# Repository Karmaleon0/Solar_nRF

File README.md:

A small solar-only, battery-free device that harvests energy using a single BPW34 cell, boosted and managing energy with the TI B5504.

Sending BLE advertisements every few seconds in direct sunlight - measuring the temperature using an exteral I2C digital chip connected to a Raytac nRF module.

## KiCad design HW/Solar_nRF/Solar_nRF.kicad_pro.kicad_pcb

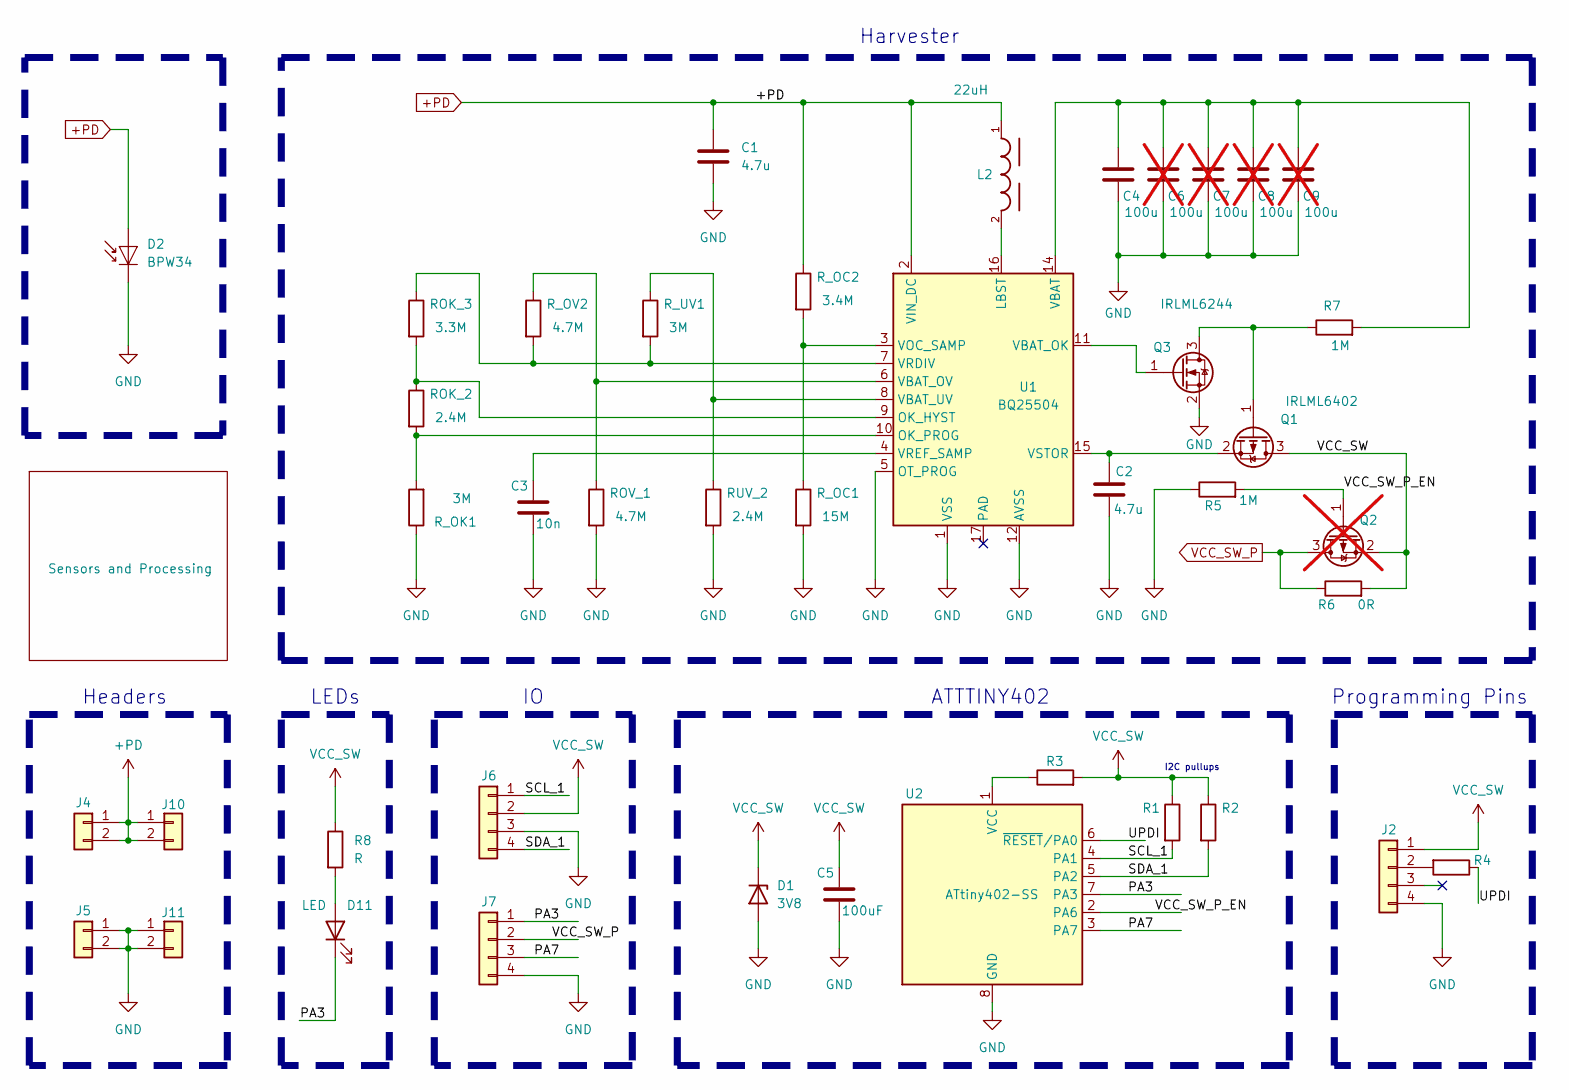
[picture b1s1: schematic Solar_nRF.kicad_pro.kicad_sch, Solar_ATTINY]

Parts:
C1, C2: 4.7u; C_0805_2012Metric_Pad1.18x1.45mm_HandSolder
C3: 10n; C_0603_1608Metric_Pad1.08x0.95mm_HandSolder
C4: 100u; C_1206_3216Metric_Pad1.33x1.80mm_HandSolder
C5: 100uF; C_1206_3216Metric_Pad1.33x1.80mm_HandSolder
C6, C7, C8, C9: 100u; C_1206_3216Metric_Pad1.33x1.80mm_HandSolder; not fitted
D1: 3V8; D_SOD-123F
D2: BPW34; Osram_DIL2_4.3x4.65mm_P5.08mm
D11: LED; LED_0805_2012Metric_Pad1.15x1.40mm_HandSolder
J2, J6, J7: Conn_01x04; PinHeader_1x04_P2.54mm_Vertical
J4, J5, J10, J11: Conn_01x02; PinSocket_1x02_P2.54mm_Vertical
L2: 22uH; WE-TPC_2828
Q1: IRLML6402; SOT-23
Q2: IRLML6402; SOT-23; not fitted
Q3: IRLML6244; SOT-23
R1, R2, R4: R; R_0603_1608Metric_Pad0.98x0.95mm_HandSolder
R3, R6: 0R; R_0603_1608Metric_Pad0.98x0.95mm_HandSolder
R5, R7: 1M; R_0603_1608Metric_Pad0.98x0.95mm_HandSolder
R8: R; R_0805_2012Metric_Pad1.20x1.40mm_HandSolder
ROK_2: 2.4M; R_0603_1608Metric_Pad0.98x0.95mm_HandSolder
ROK_3: 3.3M; R_0603_1608Metric_Pad0.98x0.95mm_HandSolder
ROV_1: 4.7M; R_0603_1608Metric_Pad0.98x0.95mm_HandSolder
RUV_2: 2.4M; R_0603_1608Metric_Pad0.98x0.95mm_HandSolder
R_OC1: 15M; R_0603_1608Metric_Pad0.98x0.95mm_HandSolder
R_OC2: 3.4M; R_0603_1608Metric_Pad0.98x0.95mm_HandSolder
R_OK1: 3M; R_0603_1608Metric_Pad0.98x0.95mm_HandSolder
R_OV2: 4.7M; R_0603_1608Metric_Pad0.98x0.95mm_HandSolder
R_UV1: 3M; R_0603_1608Metric_Pad0.98x0.95mm_HandSolder
U1: BQ25504; VQFN-16-1EP_3x3mm_P0.5mm_EP1.68x1.68mm
U2: ATtiny402-SS; SOIC-8_3.9x4.9mm_P1.27mm

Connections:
+PD: C1.1, D2.2 (A), J4.1, J4.2, J10.1, J10.2, L2.1, R_OC2.1, U1.2 (VIN_DC); also elsewhere on the board
/PA3: D11.1 (K), J7.1, U2.7 (PA3)
/PA7: J7.3, U2.3 (PA7)
/SCL_1: J6.1, R1.2, U2.4 (PA1)
/SDA_1: J6.4, R2.2, U2.5 (PA2)
/UPDI: R4.1, U2.6 (~RESET/PA0)
/VCC_SW_P_EN: Q2.1 (G), R5.2, U2.2 (PA6)
GND: C1.2, C2.2, C3.1, C4.2, C5.1, C6.2, C7.2, C8.2, C9.2, D1.2 (A), D2.1 (K), J2.4, J5.1, J5.2, J6.3, J7.4, J11.1, J11.2, Q3.2 (S), R5.1, ROV_1.2, RUV_2.2, R_OC1.2, R_OK1.1, U1.1 (VSS), U1.5 (OT_PROG), U1.12 (AVSS), U1.13 (VSS), U2.8 (GND); also elsewhere on the board
unnamed: D11.2 (A), R8.2
unnamed: J2.2, R4.2
unnamed: Q1.1 (G), Q3.3 (D), R7.1
unnamed: C2.1, Q1.2 (S), U1.15 (VSTOR)
unnamed: Q3.1 (G), U1.11 (VBAT_OK)
unnamed: L2.2, U1.16 (LBST)
unnamed: ROK_2.1, ROK_3.2, U1.9 (OK_HYST)
unnamed: ROK_2.2, R_OK1.2, U1.10 (OK_PROG)
unnamed: C4.1, C6.1, C7.1, C8.1, C9.1, R7.2, U1.14 (VBAT)
unnamed: ROV_1.1, R_OV2.1, U1.6 (VBAT_OV)
unnamed: RUV_2.1, R_UV1.1, U1.8 (VBAT_UV)
unnamed: R_OC1.1, R_OC2.2, U1.3 (VOC_SAMP)
unnamed: ROK_3.1, R_OV2.2, R_UV1.2, U1.7 (VRDIV)
unnamed: C3.2, U1.4 (VREF_SAMP)
unnamed: R3.1, U2.1 (VCC)
VCC_SW: C5.2, D1.1 (K), J2.1, J6.2, Q1.3 (D), Q2.2 (S), R1.1, R2.1, R3.2, R6.2, R8.1
VCC_SW_P: J7.2, Q2.3 (D), R6.1; also elsewhere on the board

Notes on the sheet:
Programming Pins
I2C pullups
ATTTINY402
Harvester
Headers
LEDs

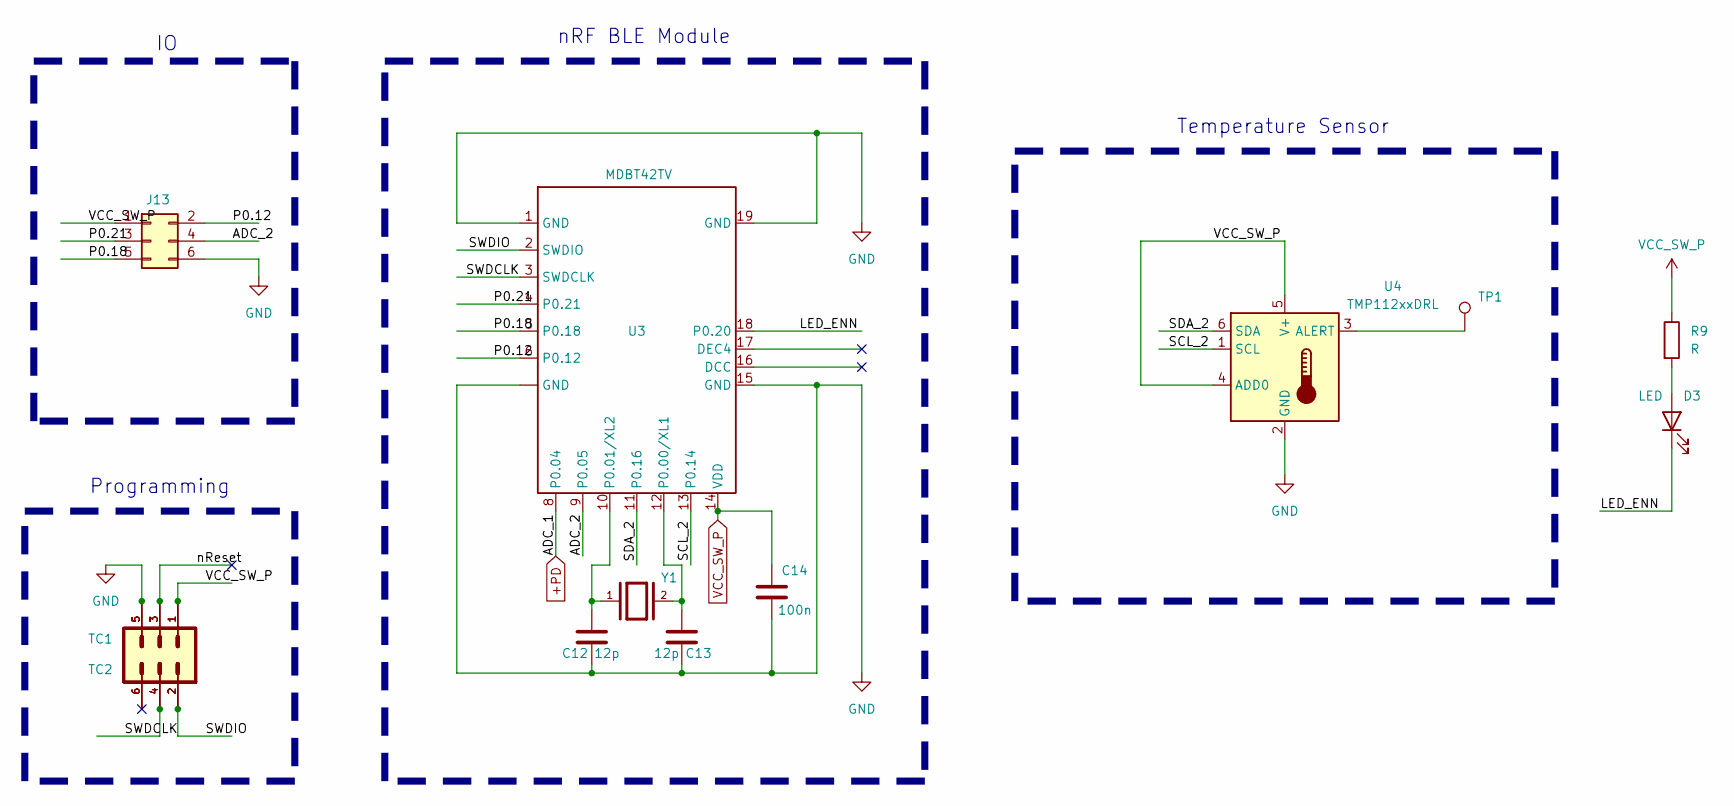
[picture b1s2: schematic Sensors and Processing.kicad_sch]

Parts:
C12, C13: 12p; C_0603_1608Metric_Pad1.08x0.95mm_HandSolder
C14: 100n; C_0805_2012Metric_Pad1.18x1.45mm_HandSolder
D3: LED; LED_0805_2012Metric_Pad1.15x1.40mm_HandSolder
J13: Conn_02x03_Odd_Even; PinHeader_2x03_P2.54mm_Vertical
R9: R; R_0805_2012Metric_Pad1.20x1.40mm_HandSolder
TC1, TC2: TC2030-IDC
TP1: TestPoint; TestPoint_Pad_D1.0mm
U3: MDBT42TV; MDBT42TV-P
U4: TMP112xxDRL; SOT-563
Y1: ABS07-32.768KHZ-T; XTAL_ABS07-32.768KHZ-T; PARTREV 08.19.15

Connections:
+PD: U3.8 (P0.04); also elsewhere on the board
/Sensors and Processing/ADC_2: J13.4, U3.9 (P0.05)
/Sensors and Processing/LED_ENN: D3.1 (K), U3.18 (P0.20)
/Sensors and Processing/P0.12: J13.2, U3.6 (P0.12)
/Sensors and Processing/P0.18: J13.5, U3.5 (P0.18)
/Sensors and Processing/P0.21: J13.3, U3.4 (P0.21)
/Sensors and Processing/SCL_2: U3.13 (P0.14), U4.1 (SCL)
/Sensors and Processing/SDA_2: U3.11 (P0.16), U4.6 (SDA)
/Sensors and Processing/SWDCLK: TC1.4, TC2.4, U3.3 (SWDCLK)
/Sensors and Processing/SWDIO: TC1.2, TC2.2, U3.2 (SWDIO)
/Sensors and Processing/nReset: TC1.3, TC2.3
GND: C12.1, C13.1, C14.2, J13.6, TC1.5, TC2.5, U3. (GND), U3.1 (GND), U3.15 (GND), U3.19 (GND), U4.2 (GND); also elsewhere on the board
unnamed: D3.2 (A), R9.2
unnamed: C13.2, U3.12 (P0.00/XL1), Y1.2
unnamed: C12.2, U3.10 (P0.01/XL2), Y1.1
unnamed: TP1.1, U4.3 (ALERT)
VCC_SW_P: C14.1, J13.1, R9.1, TC1.1, TC2.1, U3.14 (VDD), U4.4 (ADD0), U4.5 (V+); also elsewhere on the board

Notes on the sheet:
Programming
nRF BLE Module
Temperature Sensor

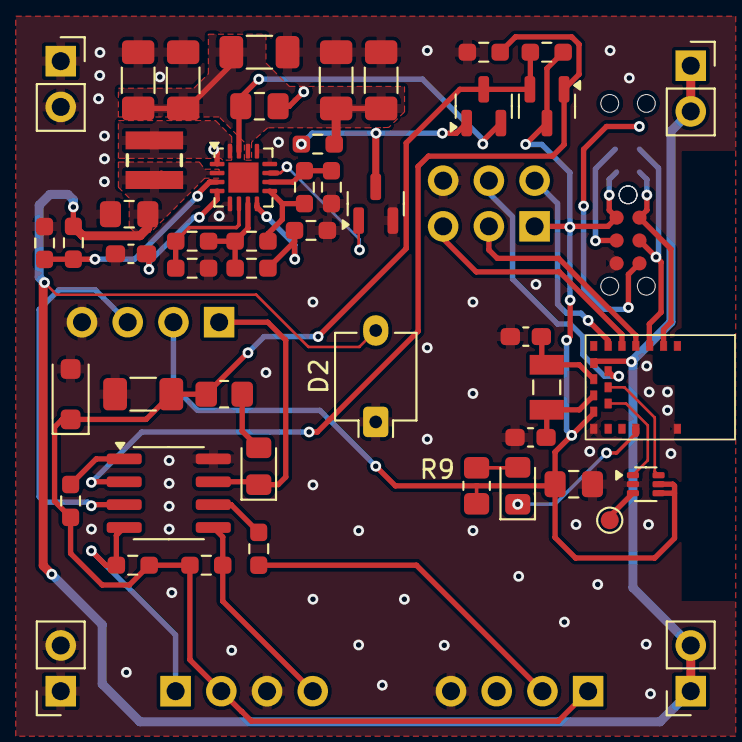
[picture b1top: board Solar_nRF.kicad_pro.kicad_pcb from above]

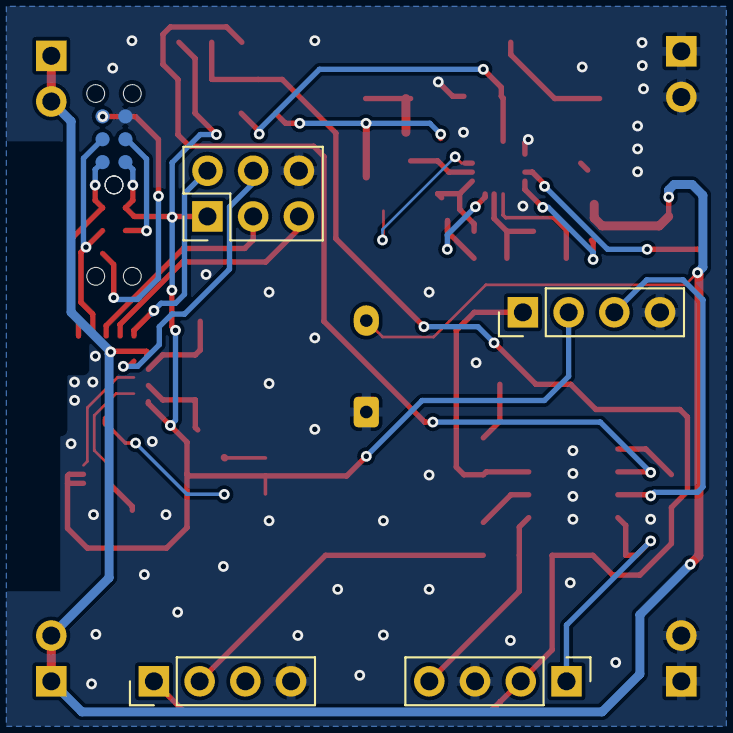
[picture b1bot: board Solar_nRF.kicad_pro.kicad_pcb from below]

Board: 2 copper layers, 54 parts (5 on the bottom side), 39 nets.

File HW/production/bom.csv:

Designator,Footprint,Quantity,Value,LCSC Part #
"C1, C2",0805,2,4.7u,
"C12, C13",0603,2,12p,
C14,0805,1,100n,
C3,0603,1,10n,
"C4, C6, C7, C8, C9",1206,5,100u,
C5,1206,1,100uF,
D1,D_SOD-123F,1,3V8,
D11,0805,1,LED,
"J10, J11, J4, J5",PinSocket_1x02_P2.54mm_Vertical,4,Conn_01x02,
J13,PinHeader_2x03_P2.54mm_Vertical,1,Conn_02x03_Odd_Even,
"J2, J6, J7",PinHeader_1x04_P2.54mm_Vertical,3,Conn_01x04,
L2,WE-TPC_2828,1,WE-TPC_2828,
"Q1, Q2",SOT-23,2,IRLML6402,
"R1, R2, R4",0603,3,R,
"R3, R6",0603,2,0R,
"R5, R7",0603,2,1M,
R8,0805,1,R,
ROK_2,0603,1,6.49M,
ROK_3,0603,1,6.0M,
ROV_1,0603,1,3.16M,
RUV_2,0603,1,1.78M,
R_OC1,0603,1,4.99M,
R_OC2,0603,1,15M,
R_OK1,0603,1,3.4M,
R_OV2,0603,1,6.19M,
R_UV1,0603,1,4.87M,
SC1,CAPPRD508W154D1200H850,1,100mF,
"TC1, TC2",TC2030-IDC,2,TC2030-IDC,
TP1,TestPoint_Pad_D1.0mm,1,TestPoint,
U1,VQFN-16-1EP_3x3mm_P0.5mm_EP1.68x1.68mm,1,BQ25504,
U2,SOIC-8_3.9x4.9mm_P1.27mm,1,ATtiny402-SS,
U3,MDBT42TV-P,1,MDBT42TV,
U4,SOT-563,1,TMP112xxDRL,
Y1,XTAL_ABS07-32.768KHZ-T,1,ABS07-32.768KHZ-T,

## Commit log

2025-07-04 Set up monorepo structure with FW, SW, and HW directories
2025-07-04 Upload for youtube
2025-07-04 Updated SCH & PCB based with fixes found during development
    Inverted bat_ok signal
    Cleaned up layout, removing solar array and replacing with a single photodiode
    Connected nRF to +V programming pad
2025-08-03 start
